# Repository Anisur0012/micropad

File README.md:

# Macropad 4x4 v2

A 16-key hot-swap macropad built around an RP2040 Pro Micro. It has per-key RGB, a rotary encoder with a push button, a 0.91" OLED, a Qwiic port and a TRRS jack. It runs QMK, and VIA support is included.

> **Status:** The PCB is routed in KiCad 9 (2 layers) and Gerbers are exported in `kicad/`. Drill files still need to be exported before ordering. The board and firmware have not been tested on real hardware yet.

## Features

- 4×4 MX layout with Kailh hot-swap sockets and 1N4148 diodes (COL2ROW)
- 16 × SK6812MINI-E reverse-mount RGB LEDs, one under each switch
- 74AHCT1G125 level shifter for the 3.3 V → 5 V LED data line
- Alps EC11E rotary encoder with push switch
- 0.91" SSD1306 128×32 OLED showing the active layer, Num/Caps Lock and RGB status
- Qwiic / STEMMA QT port (JST SH 4-pin) with 4.7 kΩ I2C pull-ups
- PJ-320D TRRS jack wired to UART (GP8/GP9), kept free for a future link
- USB-C via the controller; 2-layer, 1.6 mm board, 100 × 126 mm, 4 × M2 mounting holes

## Repository layout

| Path | Contents |
|---|---|
| `kicad/` | KiCad 9 project: schematic, routed PCB, project symbol library |
| `kicad/*.gbr`, `kicad/macropad-job.gbrjob` | Gerber files for fabrication (copper, mask, paste, silkscreen, edge cuts) |
| `Cad/macropad_assembly.step` | 3D assembly of the board, plate and case (STEP) |
| `docs/` | `schematic.pdf`, `pcb_front.png`, `pcb_back_mirrored.png` |
| `macropad_v2_firmware/firmware_source/` | QMK keyboard source (`handwired/macropad4x4v2`) |
| `macropad_v2_firmware/*.uf2` | Prebuilt firmware: `default` and `via` keymaps |
| `macropad_v2_firmware/via_macropad4x4v2.json` | VIA definition for loading the board in the VIA app |
| `macropad_v2_BOM.csv` | Bill of materials with quantities and estimated USD prices |

## Pin map

| Function | Controller pin |
|---|---|
| Rows 0–3 | GP5, GP4, GP3, GP2 |
| Columns 0–3 | GP6, GP7, GP21, GP23 |
| Encoder A / B / switch | GP26 / GP27 / GP28 |
| I2C SDA / SCL (OLED, Qwiic) | GP0 / GP1 |
| RGB data (to level shifter) | GP29 |
| TRRS UART TX / RX | GP8 / GP9 |
| Free | GP20, GP22, RST |

The LEDs are chained in a serpentine: row 0 left → right, row 1 right → left, row 2 left → right, row 3 right → left.

## Firmware

The QMK source lives in `macropad_v2_firmware/firmware_source/handwired/macropad4x4v2`. It uses a small custom matrix (`matrix.c`) that scans the 4×4 keys and adds the encoder push switch as a fifth row, so the matrix is 5 × 4.

### Flashing a prebuilt file

1. Put the board in bootloader mode: hold **BOOT** while plugging in USB, double-tap **RESET**, or press `QK_BOOT` (RGB layer, bottom-left key).
2. A drive named `RPI-RP2` appears.
3. Drag `handwired_macropad4x4v2_default.uf2` or `handwired_macropad4x4v2_via.uf2` onto it. The board reboots on its own.

### Building from source

Copy the `handwired/macropad4x4v2` folder into `keyboards/handwired/` of a QMK checkout, then run:

```sh
qmk compile -kb handwired/macropad4x4v2 -km default
qmk compile -kb handwired/macropad4x4v2 -km via
```

### Default keymap

The encoder knob sits above the grid. Pressing it is the first key in each layer.

| Layer | Encoder press | Encoder turn | Keys |
|---|---|---|---|
| 0 – Numpad | Mute | Volume down / up | Numpad 0–9, `.`, `/`, `*`, `-`, Enter. Bottom-right holds layer 1 |
| 1 – Media / Nav | Play/Pause | Previous / next track | Prev, Play, Next, arrows, Home/End, PgUp/PgDn, Num Lock, Calculator, Backspace. Top-right toggles layer 2 |
| 2 – RGB | RGB on/off | Brightness down / up | RGB toggle, mode next/previous, hue/sat/brightness/speed up and down. Bottom-left = `QK_BOOT` |
| 3 – Spare | — | — | Empty, for your own mappings |

### VIA

Flash the `via` build, open [usevia.app](https://usevia.app), and load `via_macropad4x4v2.json` under **Settings → Show Design tab → Design**. USB VID/PID: `0xFEED` / `0x4402`.

## Bill of materials

Full list with prices: [`macropad_v2_BOM.csv`](macropad_v2_BOM.csv). The estimated total is about **$238 USD** in parts, before shipping and taxes. Most of that is the case, keycaps and PCB order; the electronics alone are much cheaper.

| Qty | Refs | Part |
|---|---|---|
| 1 | — | PCB, 2-layer 1.6 mm (JLCPCB, ENIG) |
| 1 | U1 | RP2040 Pro Micro, Community Edition pinout (Sea-Picro / Elite-Pi) + 2 × 12-pin headers |
| 16 | SW1–SW16 | Kailh hot-swap socket PG151101S11 |
| 16 | D1–D16 | 1N4148, DO-35 |
| 16 | LED1–LED16 | SK6812MINI-E |
| 17 | C1–C17 | 100 nF, 0805 |
| 1 | C18 | 10 µF, 1206 |
| 1 | U2 | 74AHCT1G125, SOT-23-5 |
| 1 | R3 | 330 Ω, 0805 |
| 2 | R1, R2 | 4.7 kΩ, 0805 |
| 1 | J1 | JST SH 4-pin SM04B-SRSS-TB (Qwiic) |
| 1 | J2 | 0.91" SSD1306 128×32 I2C OLED + 4-pin female header |
| 1 | SW17 | Alps EC11E18244AU encoder with push switch + knob |
| 1 | J3 | PJ-320D TRRS jack |
| 4 | H1–H4 | M2 × 6 mm screws (+ heat-set inserts for a printed case) |
| 16 | — | MX switches (Gateron Oil King V2) + 1u keycaps |
| 1 | — | Switch plate (1.5 mm aluminium) and case (CNC aluminium or 3D printed) |

## Ordering the PCB

1. In KiCad, open `kicad/macropad.kicad_pcb` and run **Inspect → Design Rules Checker** until it reports 0 errors and 0 unconnected items.
2. Export drill files: **File → Fabrication Outputs → Drill Files** (Excellon, into the `kicad/` folder).
3. Zip the `.gbr` and `.drl` files and upload the zip to JLCPCB (2 layers, 1.6 mm, 100 × 126 mm).

## ⚠️ Check before you order or plug in

1. **Controller pinout.** It must be a Pro Micro RP2040 with the Community Edition pinout (Elite-Pi, Sea-Picro, Liatris, Frood). A Raspberry Pi Pico or RP2040-Zero will not fit.
2. **LED footprint.** The SK6812MINI-E pads follow the marbastlib layout (1 VDD, 2 DOUT, 3 GND, 4 DIN). Compare it against the datasheet of the LEDs you buy.
3. **OLED pin order.** The footprint is GND, VCC, SCL, SDA. Some modules use VCC, GND, SCL, SDA. Check yours first.
4. **TRRS.** Never plug or unplug the TRRS cable while USB is connected. Ring 2 carries 5 V.
5. **RGB power.** 16 LEDs at full white can draw about 1 A. The firmware caps brightness at 100/255 to stay within USB's 500 mA.
6. **OLED orientation.** The firmware rotates the display 180°. If yours reads upside down, change `OLED_ROTATION_180` to `OLED_ROTATION_0` in `macropad4x4v2.c`.

## Credits

- Hot-swap pad geometry: ai03 MX_Alps_Hybrid
- SK6812MINI-E pad layout and cutout: marbastlib by ebastler (CERN-OHL-P)
- Firmware: [QMK](https://qmk.fm), GPL-2.0-or-later

Designed by [Sk Izaz Ahmed](https://github.com/SkIzazAhmed).

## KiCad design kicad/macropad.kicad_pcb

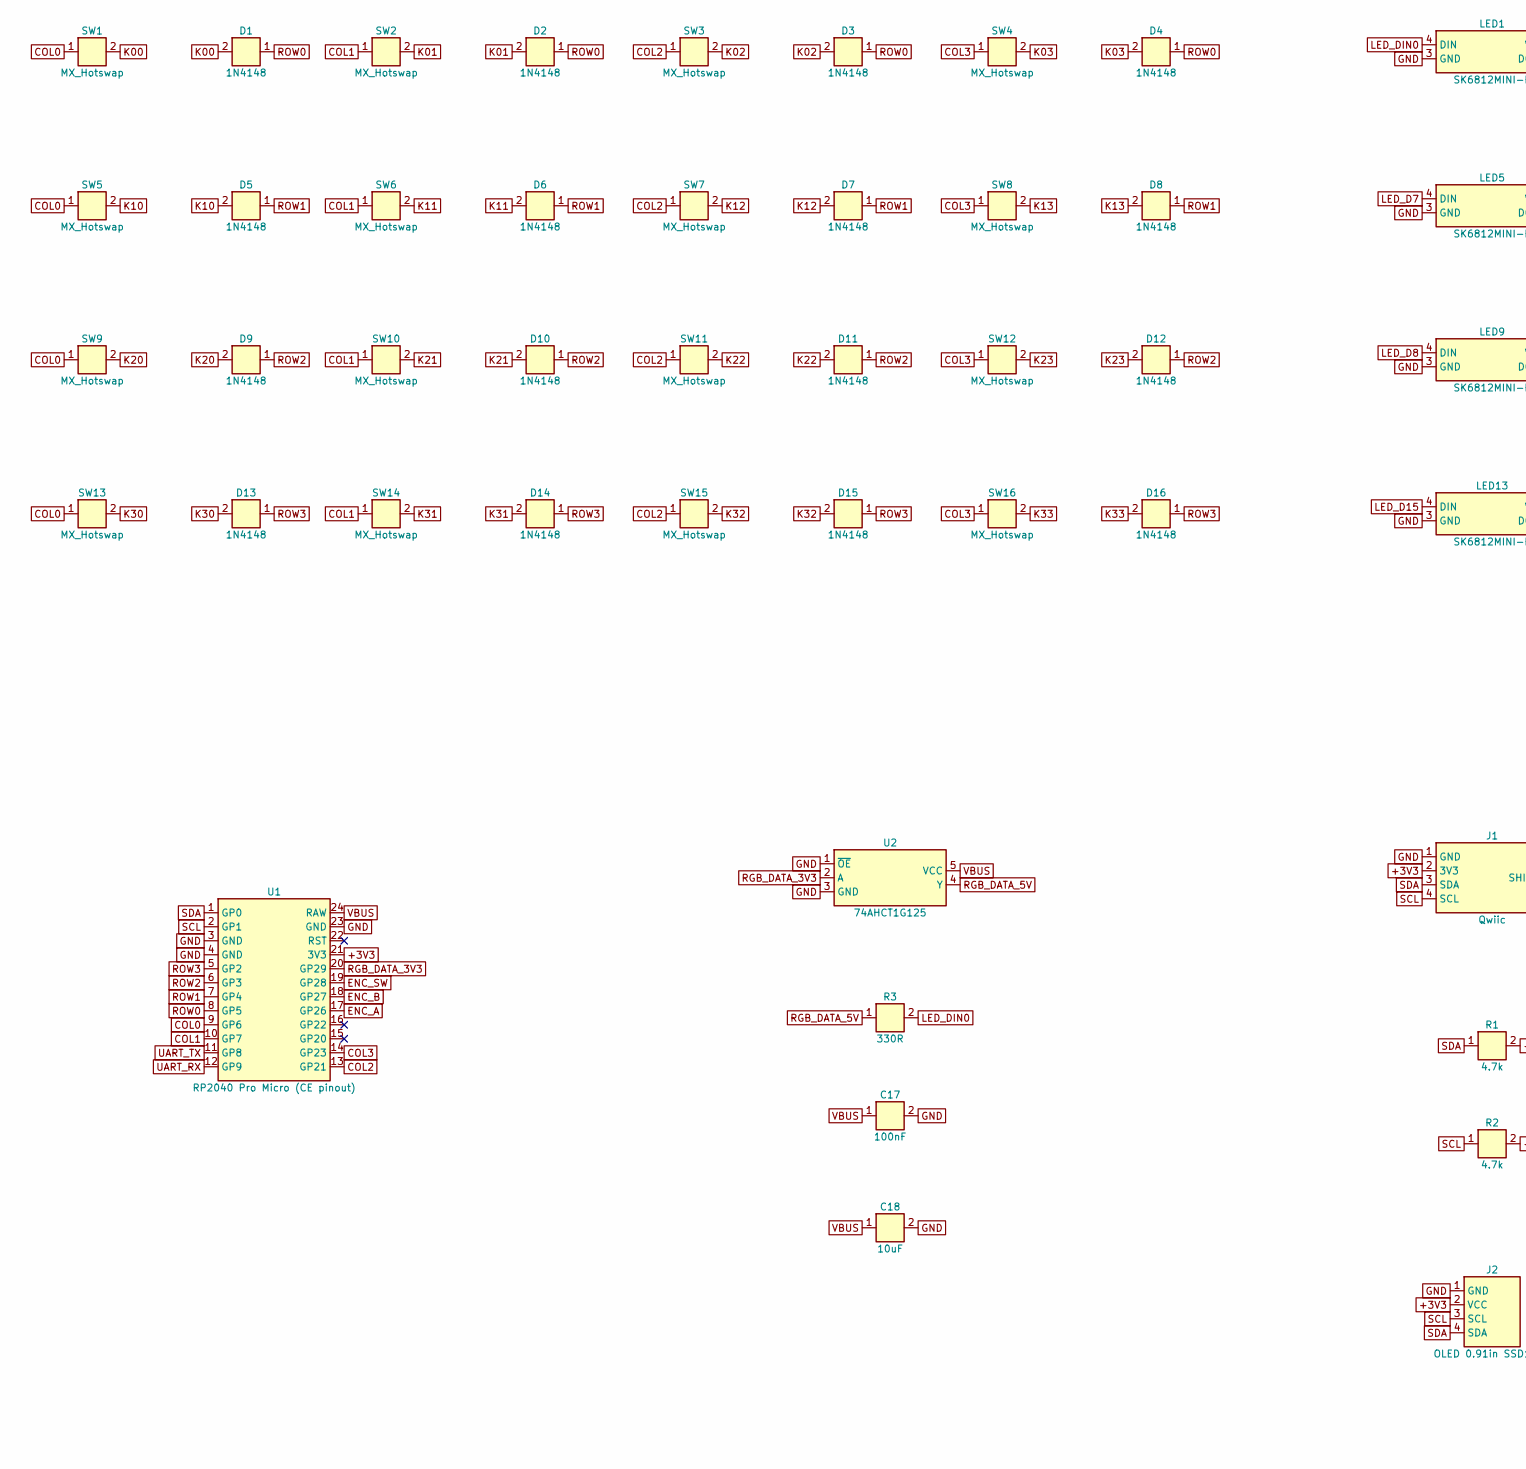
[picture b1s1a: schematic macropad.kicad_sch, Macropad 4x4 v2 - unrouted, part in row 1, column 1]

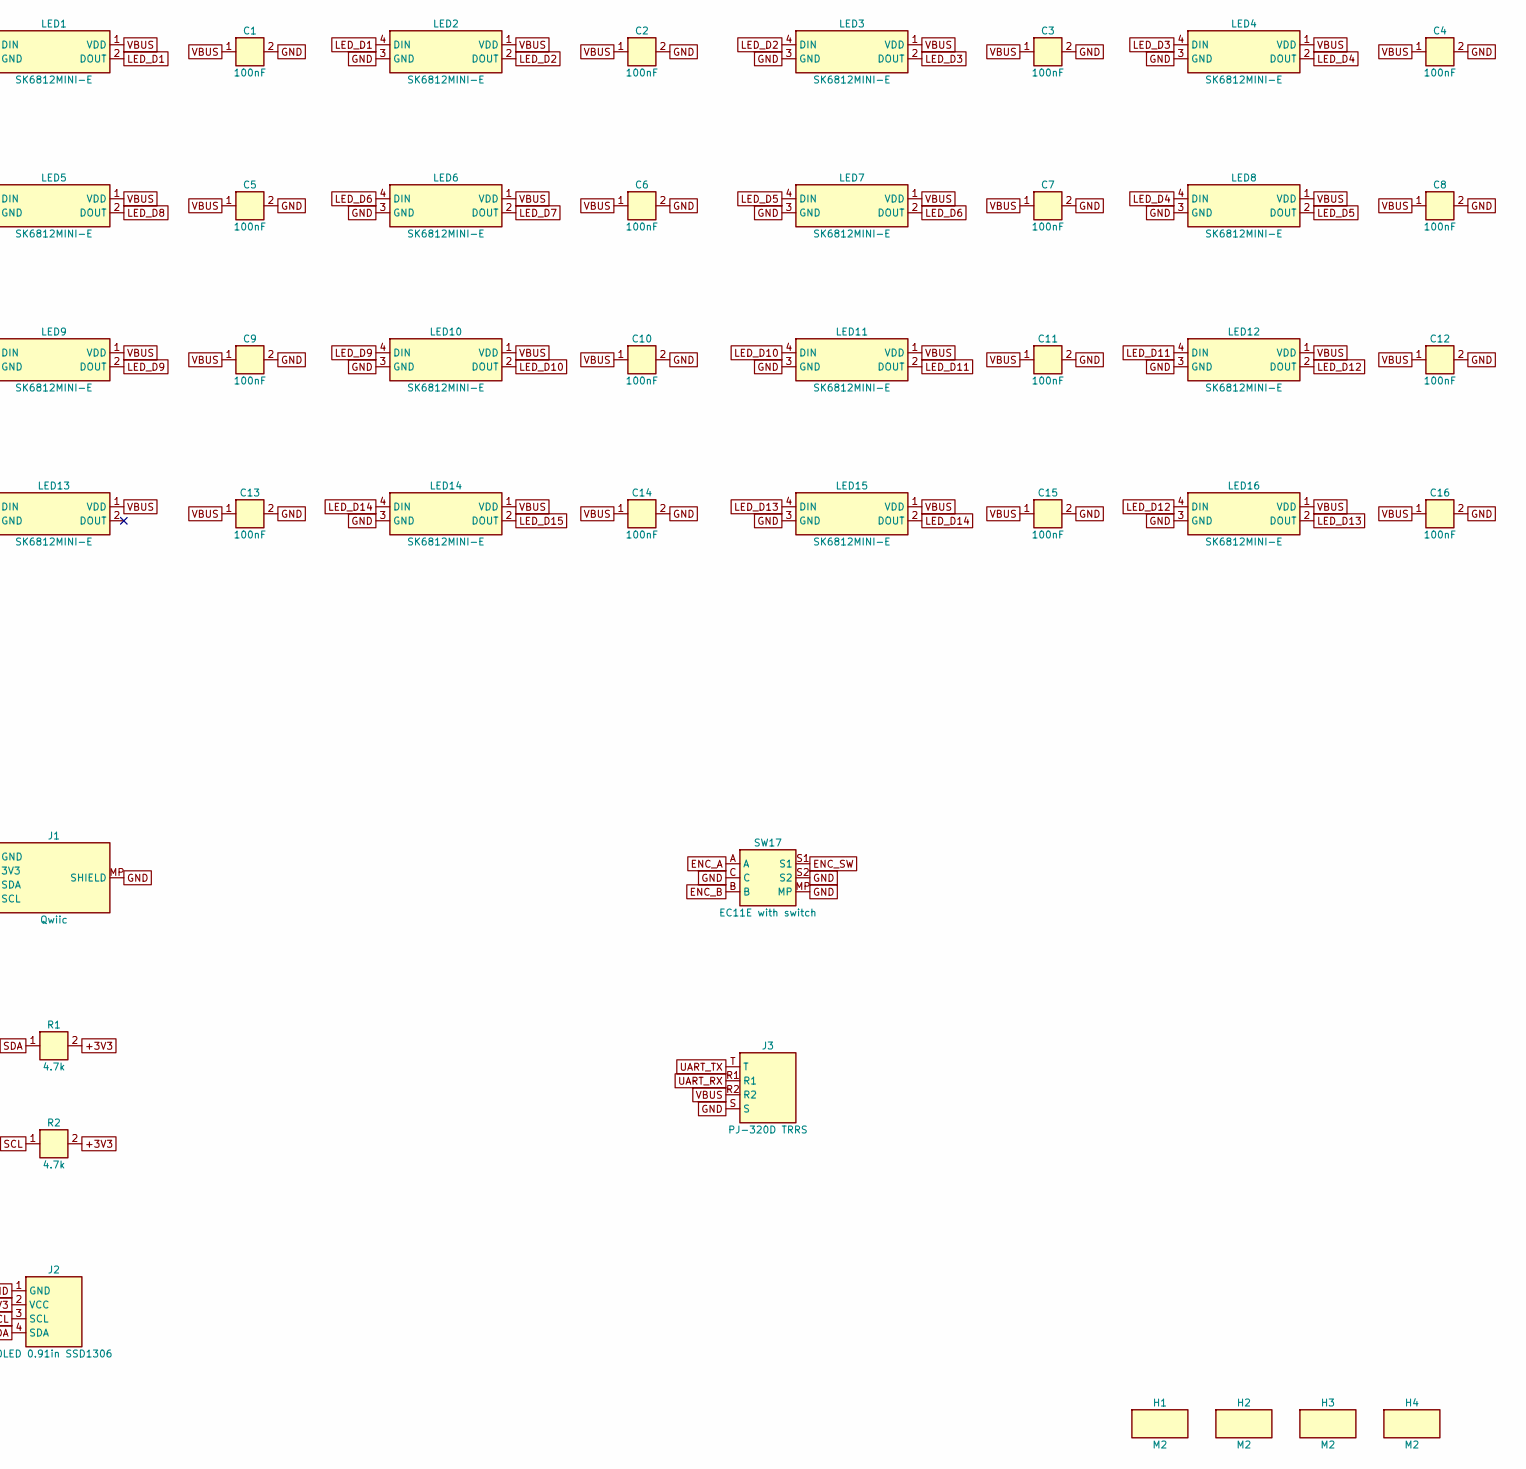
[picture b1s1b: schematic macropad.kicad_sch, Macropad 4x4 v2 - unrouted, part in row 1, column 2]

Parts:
C1, C2, C3, C4, C5, C6, C7, C8, C9, C10, C11, C12, C13, C14, C15, C16, C17: 100nF; C_0805_2012Metric_Pad1.18x1.45mm_HandSolder
C18: 10uF; C_1206_3216Metric_Pad1.33x1.80mm_HandSolder
D1, D2, D3, D4, D5, D6, D7, D8, D9, D10, D11, D12, D13, D14, D15, D16: 1N4148; D_DO-35_SOD27_P7.62mm_Horizontal
H1, H2, H3, H4: M2; MountingHole_2.2mm_M2
J1: Qwiic; JST_SH_SM04B-SRSS-TB_1x04-1MP_P1.00mm_Horizontal
J2: OLED 0.91in SSD1306; OLED_0.91in_128x32_Header
J3: PJ-320D TRRS; Jack_3.5mm_PJ320D_Horizontal
LED1, LED2, LED3, LED4, LED5, LED6, LED7, LED8, LED9, LED10, LED11, LED12, LED13, LED14, LED15, LED16: SK6812MINI-E; LED_SK6812MINI-E_Reverse
R1, R2: 4.7k; R_0805_2012Metric_Pad1.20x1.40mm_HandSolder
R3: 330R; R_0805_2012Metric_Pad1.20x1.40mm_HandSolder
SW1, SW2, SW3, SW4, SW5, SW6, SW7, SW8, SW9, SW10, SW11, SW12, SW13, SW14, SW15, SW16: MX_Hotswap; SW_MX_Hotswap_Kailh_1u
SW17: EC11E with switch; RotaryEncoder_Alps_EC11E-Switch_Vertical_H20mm
U1: RP2040 Pro Micro (CE pinout); ProMicro_RP2040_CE
U2: 74AHCT1G125; SOT-23-5

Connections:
+3V3: J1.2 (3V3), J2.2 (VCC), R1.2, R2.2, U1.21 (3V3)
COL0: SW1.1, SW5.1, SW9.1, SW13.1, U1.9 (GP6)
COL1: SW2.1, SW6.1, SW10.1, SW14.1, U1.10 (GP7)
COL2: SW3.1, SW7.1, SW11.1, SW15.1, U1.13 (GP21)
COL3: SW4.1, SW8.1, SW12.1, SW16.1, U1.14 (GP23)
ENC_A: SW17.A, U1.17 (GP26)
ENC_B: SW17.B, U1.18 (GP27)
ENC_SW: SW17.S1, U1.19 (GP28)
GND: C1.2, C2.2, C3.2, C4.2, C5.2, C6.2, C7.2, C8.2, C9.2, C10.2, C11.2, C12.2, C13.2, C14.2, C15.2, C16.2, C17.2, C18.2, J1.1 (GND), J1.MP (SHIELD), J2.1 (GND), J3.S, LED1.3 (GND), LED2.3 (GND), LED3.3 (GND), LED4.3 (GND), LED5.3 (GND), LED6.3 (GND), LED7.3 (GND), LED8.3 (GND), LED9.3 (GND), LED10.3 (GND), LED11.3 (GND), LED12.3 (GND), LED13.3 (GND), LED14.3 (GND), LED15.3 (GND), LED16.3 (GND), SW17.C, SW17.MP, SW17.S2, U1.3 (GND), U1.4 (GND), U1.23 (GND), U2.1 (~OE), U2.3 (GND)
K00: D1.2 (A), SW1.2
K01: D2.2 (A), SW2.2
K02: D3.2 (A), SW3.2
K03: D4.2 (A), SW4.2
K10: D5.2 (A), SW5.2
K11: D6.2 (A), SW6.2
K12: D7.2 (A), SW7.2
K13: D8.2 (A), SW8.2
K20: D9.2 (A), SW9.2
K21: D10.2 (A), SW10.2
K22: D11.2 (A), SW11.2
K23: D12.2 (A), SW12.2
K30: D13.2 (A), SW13.2
K31: D14.2 (A), SW14.2
K32: D15.2 (A), SW15.2
K33: D16.2 (A), SW16.2
LED_D1: LED1.2 (DOUT), LED2.4 (DIN)
LED_D2: LED2.2 (DOUT), LED3.4 (DIN)
LED_D3: LED3.2 (DOUT), LED4.4 (DIN)
LED_D4: LED4.2 (DOUT), LED8.4 (DIN)
LED_D5: LED7.4 (DIN), LED8.2 (DOUT)
LED_D6: LED6.4 (DIN), LED7.2 (DOUT)
LED_D7: LED5.4 (DIN), LED6.2 (DOUT)
LED_D8: LED5.2 (DOUT), LED9.4 (DIN)
LED_D9: LED9.2 (DOUT), LED10.4 (DIN)
LED_D10: LED10.2 (DOUT), LED11.4 (DIN)
LED_D11: LED11.2 (DOUT), LED12.4 (DIN)
LED_D12: LED12.2 (DOUT), LED16.4 (DIN)
LED_D13: LED15.4 (DIN), LED16.2 (DOUT)
LED_D14: LED14.4 (DIN), LED15.2 (DOUT)
LED_D15: LED13.4 (DIN), LED14.2 (DOUT)
LED_DIN0: LED1.4 (DIN), R3.2
RGB_DATA_3V3: U1.20 (GP29), U2.2 (A)
RGB_DATA_5V: R3.1, U2.4 (Y)
ROW0: D1.1 (K), D2.1 (K), D3.1 (K), D4.1 (K), U1.8 (GP5)
ROW1: D5.1 (K), D6.1 (K), D7.1 (K), D8.1 (K), U1.7 (GP4)
ROW2: D9.1 (K), D10.1 (K), D11.1 (K), D12.1 (K), U1.6 (GP3)
ROW3: D13.1 (K), D14.1 (K), D15.1 (K), D16.1 (K), U1.5 (GP2)
SCL: J1.4 (SCL), J2.3 (SCL), R2.1, U1.2 (GP1)
SDA: J1.3 (SDA), J2.4 (SDA), R1.1, U1.1 (GP0)
UART_RX: J3.R1, U1.12 (GP9)
UART_TX: J3.T, U1.11 (GP8)
VBUS: C1.1, C2.1, C3.1, C4.1, C5.1, C6.1, C7.1, C8.1, C9.1, C10.1, C11.1, C12.1, C13.1, C14.1, C15.1, C16.1, C17.1, C18.1, J3.R2, LED1.1 (VDD), LED2.1 (VDD), LED3.1 (VDD), LED4.1 (VDD), LED5.1 (VDD), LED6.1 (VDD), LED7.1 (VDD), LED8.1 (VDD), LED9.1 (VDD), LED10.1 (VDD), LED11.1 (VDD), LED12.1 (VDD), LED13.1 (VDD), LED14.1 (VDD), LED15.1 (VDD), LED16.1 (VDD), U1.24 (RAW), U2.5 (VCC)

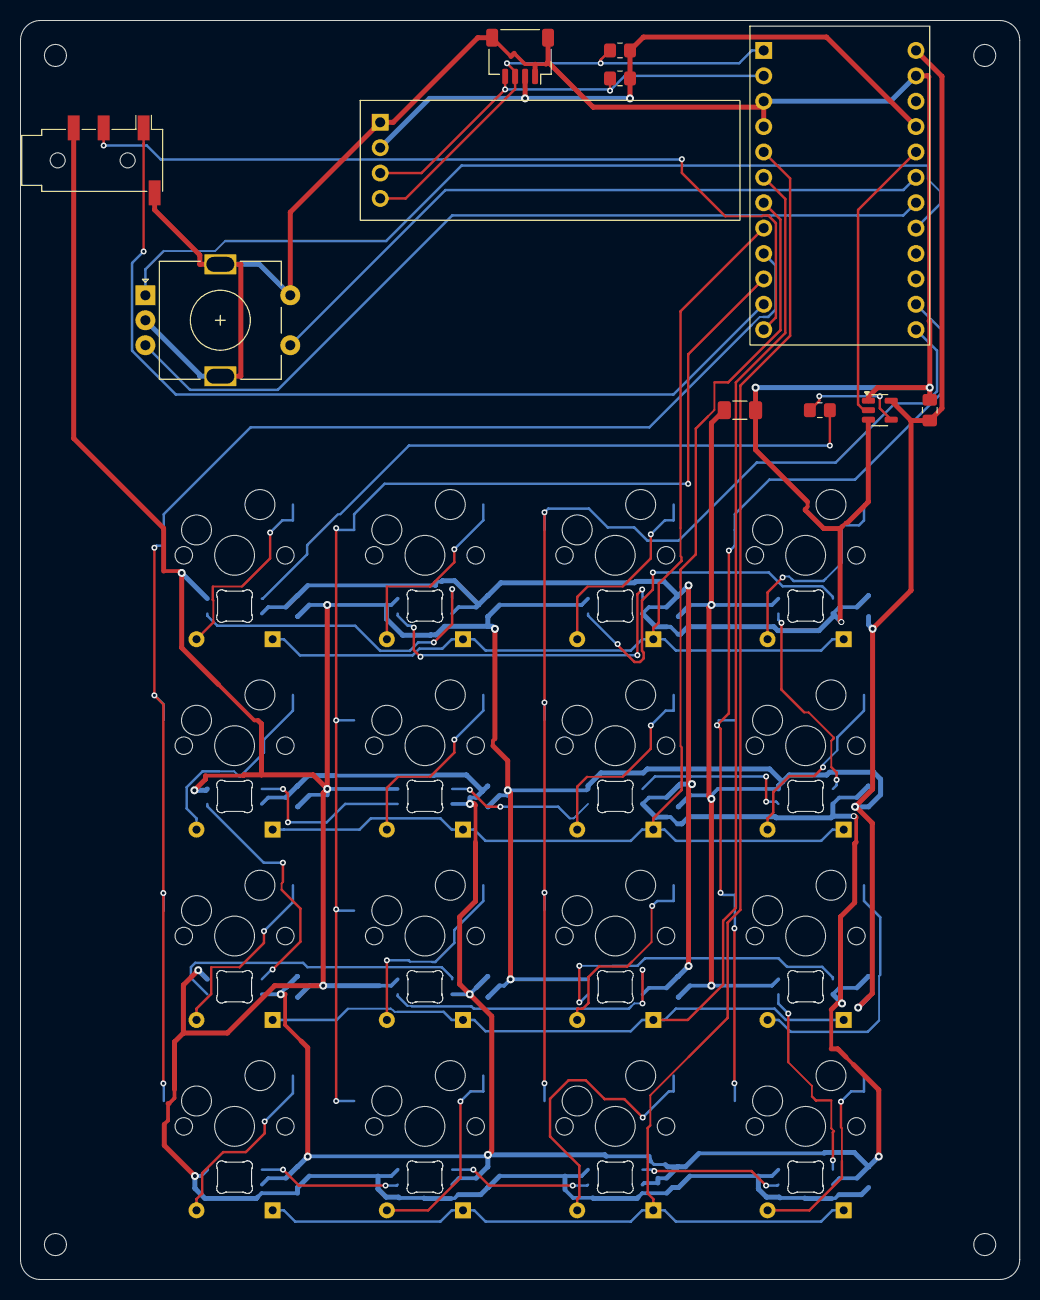
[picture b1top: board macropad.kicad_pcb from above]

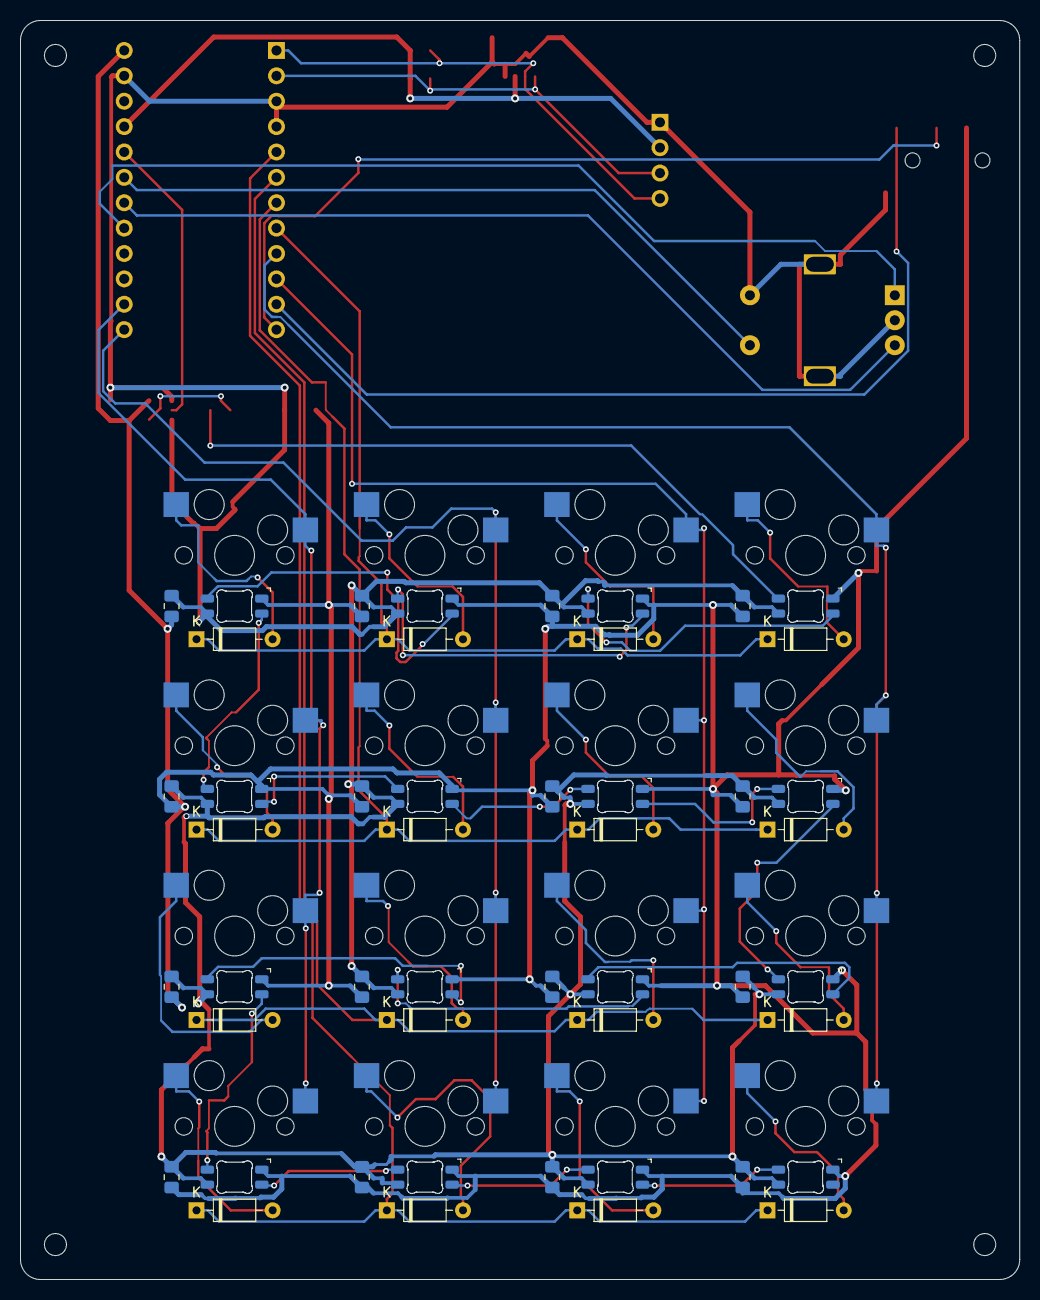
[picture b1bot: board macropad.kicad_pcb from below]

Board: 2 copper layers, 100.0 x 126.0 mm, 79 parts (64 on the bottom side), 52 nets.

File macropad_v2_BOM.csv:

Qty needed,Refs,Part,Pick,Buy qty (incl. spares),Unit,Unit price (USD),Line total (USD),Price source
1,PCB,PCB 2-layer 1.6mm,JLCPCB ENIG matte black (min order 5),1,pack of 5,25.00,25.00,Estimate
1,U1,Controller,Sea-Picro or Elite-Pi (RP2040 Pro Micro CE),1,each,17.00,17.00,Estimate
2,U1,Pin headers,12-pin 2.54mm male,2,each,0.5,1.00,Estimate
16,SW1-SW16,Hot-swap sockets,Kailh PG151101S11,1,pack of 100,10.00,10.00,Divinikey
16,D1-D16,Diodes,1N4148 DO-35 (Vishay/onsemi),20,each,0.1,2.00,Estimate
16,-,Switches,Gateron Oil King V2 (linear),2,pack of 10,6.50,13.00,Milktooth
16,-,Keycaps,GMK or thick PBT 1u,1,set,45.00,45.00,Estimate
1,-,Switch plate,Aluminium laser-cut 1.5mm,1,each,20.00,20.00,Estimate
1,-,Case,CNC aluminium (or 3D print ~$3),1,each,60.00,60.00,Estimate
4,H1-H4,Screws,Stainless M2 x 6mm,1,pack,3.00,3.00,Estimate
4,-,Heat-set inserts,M2 brass (printed case only),1,pack,3.00,3.00,Estimate
4,-,Feet,10mm silicone bumpons,1,pack,2.00,2.00,Estimate
1,-,USB cable,Good USB-C cable,1,each,10.00,10.00,Estimate
1,J1,Qwiic connector,JST SH SM04B-SRSS-TB,2,each,0.6,1.20,Estimate
2,R1-R2,Resistors,4.7k 0805,5,each,0.05,0.25,Estimate
2,-,Qwiic cables,100mm JST SH 4-pin,2,each,1.00,2.00,Estimate
1,J2,OLED display,0.91in SSD1306 128x32 I2C (GND VCC SCL SDA),1,each,5.99,5.99,Tindie (ICStation)
1,J2,Female header,4-pin 2.54mm,1,each,0.5,0.50,Estimate
1,SW17,Rotary encoder,Alps EC11E18244AU with push switch,1,each,4.49,4.49,DigiKey
1,-,Encoder knob,Aluminium 6mm D-shaft,1,each,4.00,4.00,Estimate
1,J3,TRRS jack,PJ-320D,2,each,0.5,1.00,Estimate
1,-,TRRS cable,3.5mm 4-pole,1,each,4.00,4.00,Estimate
16,LED1-LED16,RGB LEDs,SK6812MINI-E,20,each,0.0853,1.71,LCSC (5+ price)
17,C1-C17,Capacitors,100nF 0805,20,each,0.02,0.40,Estimate
1,C18,Capacitor,10uF 1206,2,each,0.1,0.20,Estimate
1,U2,Level shifter,74AHCT1G125 SOT-23-5,2,each,0.3,0.60,Estimate
1,R3,Resistor,330R 0805,5,each,0.05,0.25,Estimate

,,"TOTAL (parts only, excl. shipping/taxes/import duty)",,,,,237.59,
